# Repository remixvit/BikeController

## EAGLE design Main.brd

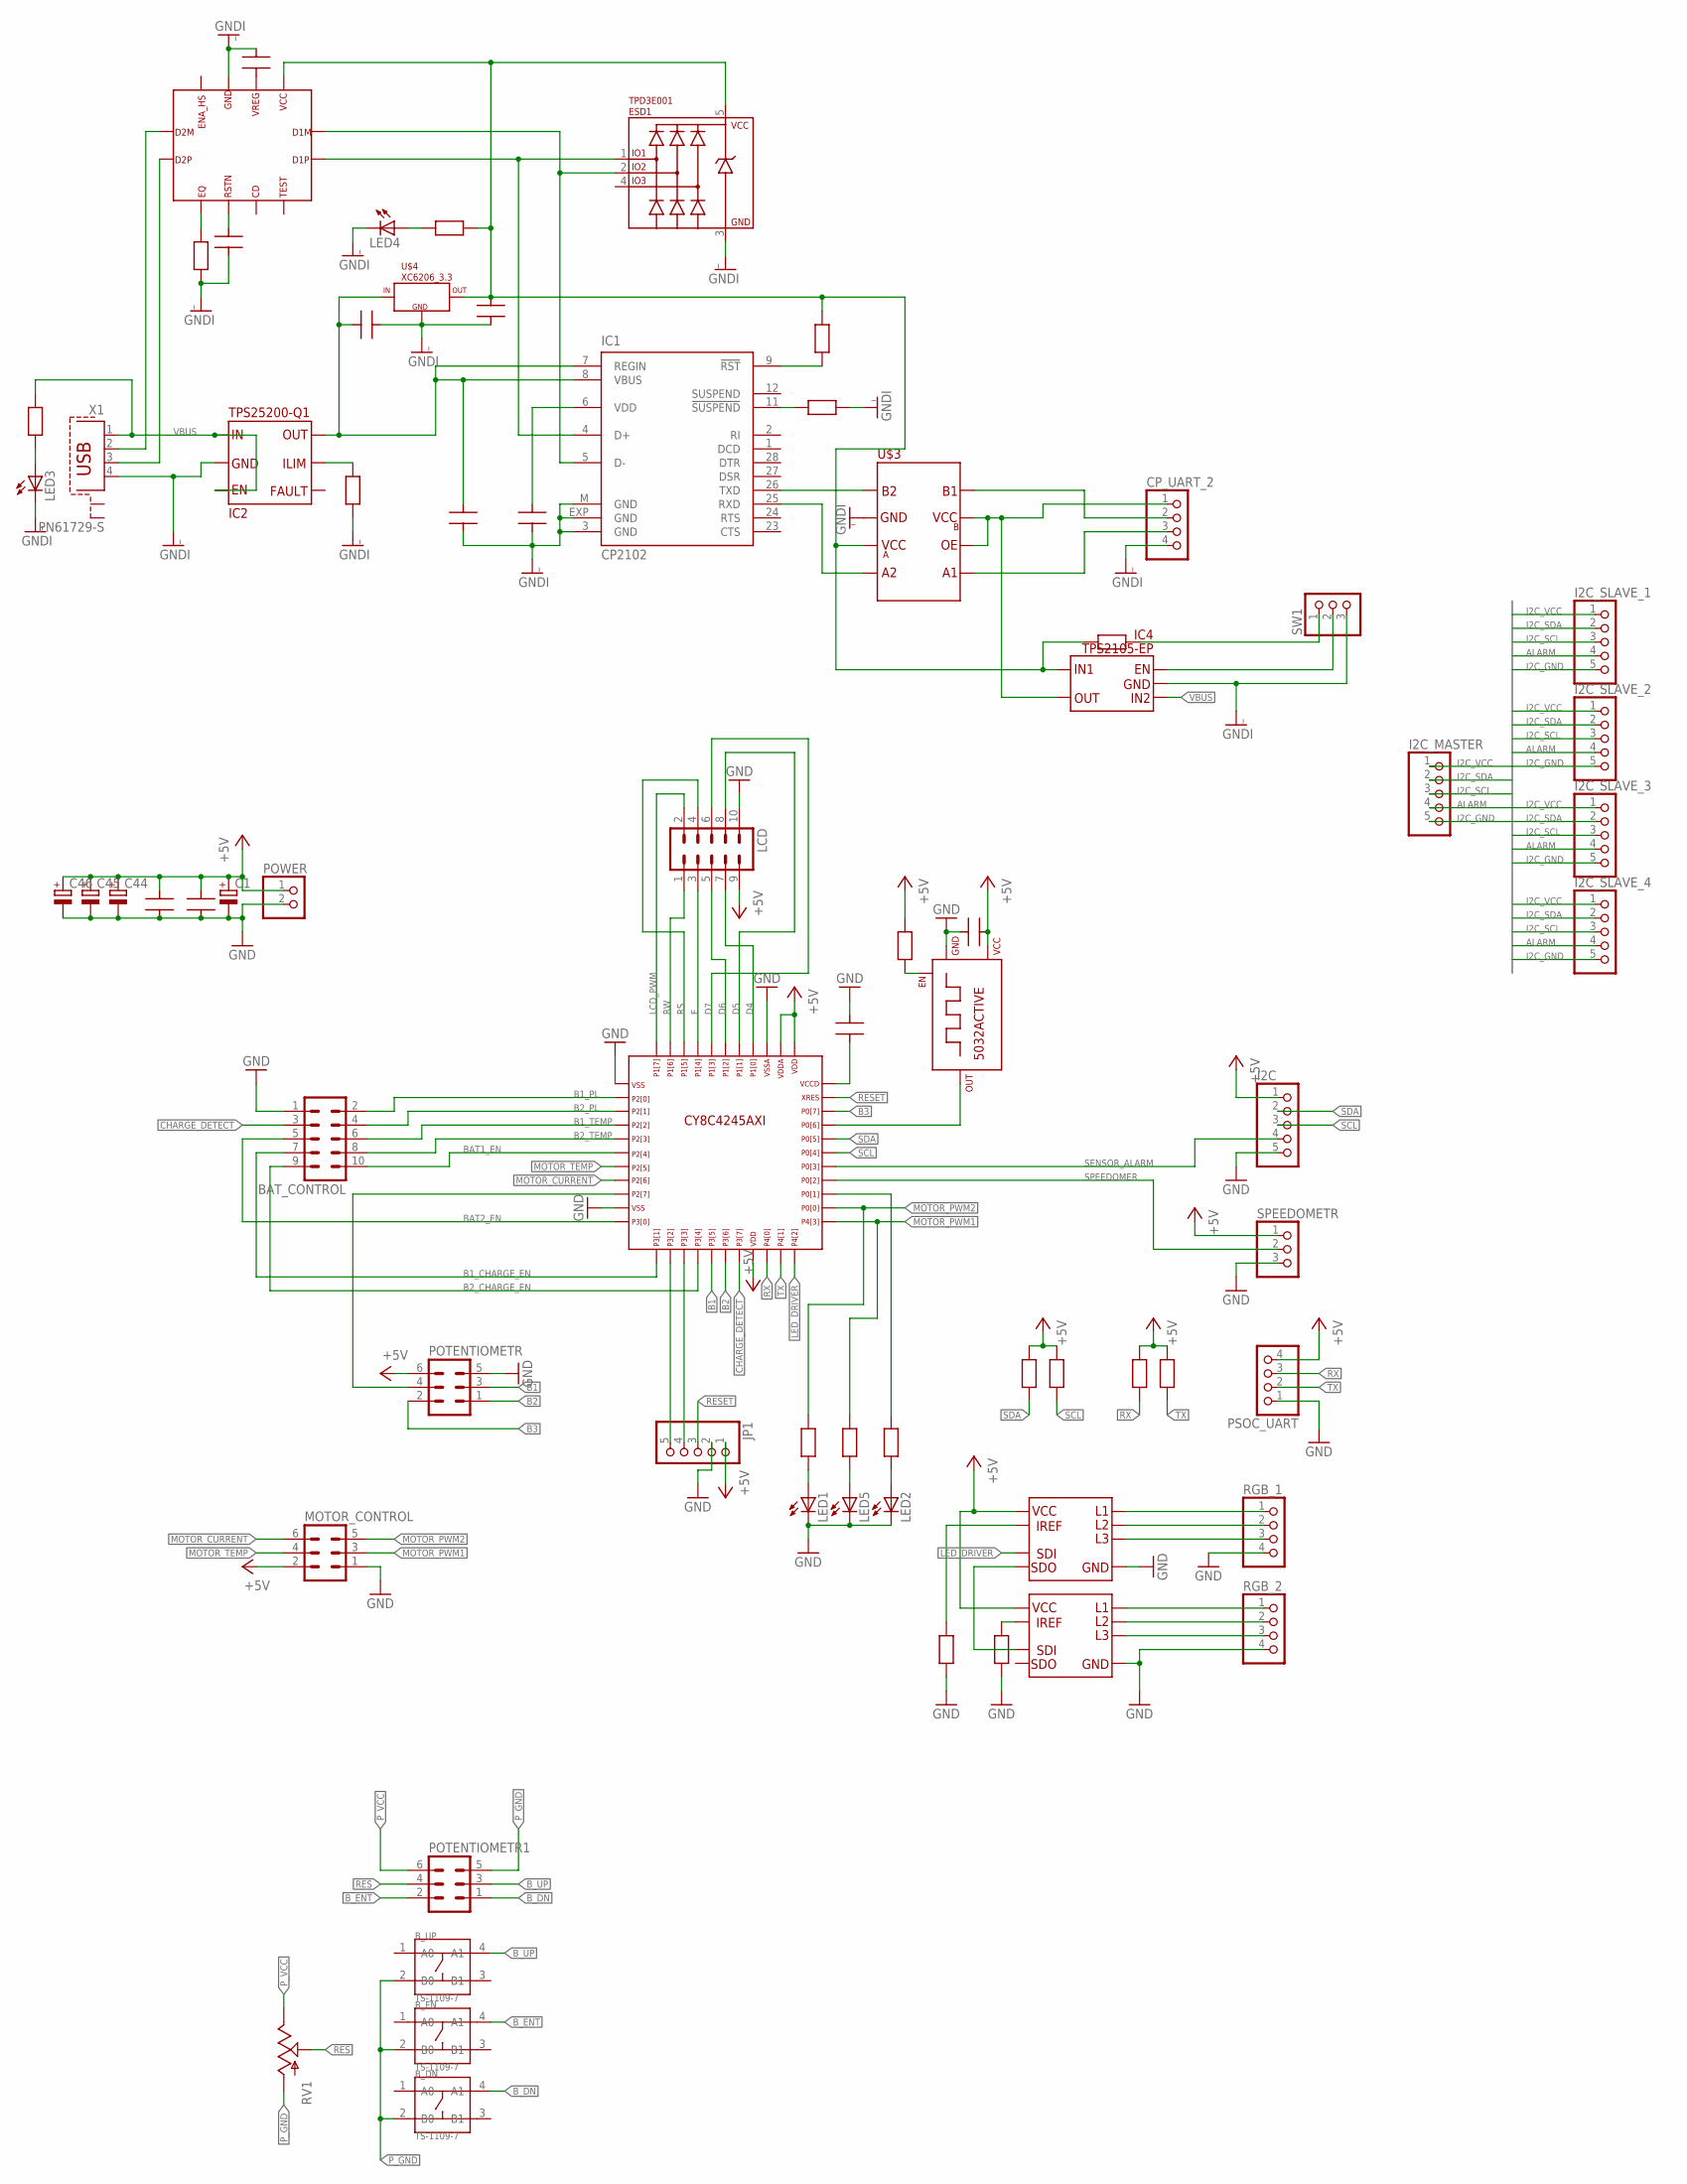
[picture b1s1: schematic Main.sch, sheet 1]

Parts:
BAT_CONTROL: ML10
B_DN: TS-1109-7; SW4-6.2X6.2X5.0MM
B_EN: TS-1109-7; SW4-6.2X6.2X5.0MM
B_UP: TS-1109-7; SW4-6.2X6.2X5.0MM
C1, C44: CPOL-EU150CLZ-0810; 150CLZ-0810
C2, C3, C4, C5, C6, C7, C8, C9, C10, C11: CAP0603; C0603
C45, C46: CPOL-EUSMCD; SMC_D
CP_UART_2: PINHD-1X4; 1X04
ESD1: TPD3E001; SOT23-5
I2C, I2C_MASTER, I2C_SLAVE_1, I2C_SLAVE_2, I2C_SLAVE_3, I2C_SLAVE_4: PINHD-1X5; 1X05
IC1: CP2102; MLP28
IC2: TPS25200-Q1; PWSON6
IC4: TPS2105-EP; SOT23-5
JP1: PINHD-1X5; 1X05
LCD: ML10
LED1, LED2, LED5: LEDCHIP-LED0603; CHIP-LED0603
LED3, LED4: LEDCHIP-LED0805; CHIP-LED0805
LED_DR1, LED_DR2: TLC5973; SOIC8-1.27-5X4MM
MOTOR_CONTROL: ML6
POTENTIOMETR, POTENTIOMETR1: ML6
POWER: PINHD-1X2; 1X02
PSOC_UART: PINHD-1X4; 1X04
R1, R2, R3, R4, R5, R6, R7, R8, R9, R10, R11, R12, R13, R14, R15, R16, R41: RES0603; R0603
RGB_1, RGB_2: PINHD-1X4; 1X04
RV1: POT; ALPS_POT
SPEEDOMETR: PINHD-1X3; 1X03
SW1: PINHD-1X3; 1X03
U$1: CY8C4245; TQFP44_CY_LOGO
U$2: 5032ACTIVE; 5030A
U$3: TXS0102_SM8; SM8
U$4: XC6206_3.3; SOT23
USB1: TUSB211QRWBRQ1; X2QFN
X1: PN61729-S

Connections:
+5V: C1.+, C2.2, C3.2, C5.2, C44.+, C45.+, C46.+, I2C.1, JP1.1, LCD.9, LED_DR1.8, LED_DR2.8, MOTOR_CONTROL.2, POTENTIOMETR.6, POWER.1, PSOC_UART.4, R1.2, R2.2, R3.2, R4.2, R7.2, SPEEDOMETR.1, U$1.19, U$1.34, U$1.35, U$2.4 (+5V)
ALARM: I2C_MASTER.4, I2C_SLAVE_1.4, I2C_SLAVE_2.4, I2C_SLAVE_3.4, I2C_SLAVE_4.4
B1: POTENTIOMETR.3, U$1.16
B1_CHARGE_EN: BAT_CONTROL.7, U$1.12
B1_PL: BAT_CONTROL.2, U$1.2
B1_TEMP: BAT_CONTROL.6, U$1.4
B2: POTENTIOMETR.1, U$1.17
B2_CHARGE_EN: BAT_CONTROL.9, U$1.15
B2_PL: BAT_CONTROL.4, U$1.3
B2_TEMP: BAT_CONTROL.8, U$1.5
B3: POTENTIOMETR.2, U$1.31
BAT1_EN: BAT_CONTROL.10, U$1.6
BAT2_EN: BAT_CONTROL.5, U$1.11
B_DN: B_DN.4 (A1), POTENTIOMETR1.1
B_ENT: B_EN.4 (A1), POTENTIOMETR1.2
B_UP: B_UP.4 (A1), POTENTIOMETR1.3
CHARGE_DETECT: BAT_CONTROL.3, U$1.18
D4: LCD.7, U$1.37
D5: LCD.8, U$1.38
D6: LCD.5, U$1.39
D7: LCD.6, U$1.40
E: LCD.3, U$1.41
GND: BAT_CONTROL.1, C1.-, C2.1, C3.1, C4.1, C5.1, C44.-, C45.-, C46.-, I2C.5, JP1.2, LCD.10, LED1.C, LED2.C, LED5.C, LED_DR1.4, LED_DR2.4, MOTOR_CONTROL.1, POTENTIOMETR.5, POWER.2, PSOC_UART.1, R10.1, R11.1, RGB_1.4, RGB_2.4, SPEEDOMETR.3, U$1.1, U$1.10, U$1.36, U$2.2 (GND)
GNDI: C6.1, C7.1, C8.1, C9.2, C10.1, C11.2, CP_UART_2.4, ESD1.3, IC1.3 (GND), IC1.EXP (GND), IC1.M (GND), IC2.EPAD, IC2.P$2, IC4.2, LED3.C, LED4.C, R9.1, R12.1, R15.1, SW1.3, U$3.GND, U$4.1 (GND), USB1.10, X1.4
I2C_GND: I2C_MASTER.5, I2C_SLAVE_1.5, I2C_SLAVE_2.5, I2C_SLAVE_3.5, I2C_SLAVE_4.5
I2C_SCL: I2C_MASTER.3, I2C_SLAVE_1.3, I2C_SLAVE_2.3, I2C_SLAVE_3.3, I2C_SLAVE_4.3
I2C_SDA: I2C_MASTER.2, I2C_SLAVE_1.2, I2C_SLAVE_2.2, I2C_SLAVE_3.2, I2C_SLAVE_4.2
I2C_VCC: I2C_MASTER.1, I2C_SLAVE_1.1, I2C_SLAVE_2.1, I2C_SLAVE_3.1, I2C_SLAVE_4.1
LCD_PWM: LCD.2, U$1.44
LED_DRIVER: LED_DR1.6, U$1.22
MOTOR_CURRENT: MOTOR_CONTROL.6, U$1.8
MOTOR_PWM1: MOTOR_CONTROL.3, R41.2, U$1.23
MOTOR_PWM2: MOTOR_CONTROL.5, R5.2, U$1.24
MOTOR_TEMP: MOTOR_CONTROL.4, U$1.7
unnamed: U$1.30, U$2.3 (OUT)
unnamed: C4.2, U$1.33
unnamed: JP1.5, U$1.13
unnamed: JP1.4, U$1.14
unnamed: IC2.P$1, IC2.P$3, R13.2, X1.1
unnamed: R6.2, U$1.25
unnamed: POTENTIOMETR.4, U$1.9
unnamed: R7.1, U$2.1 (EN)
unnamed: C9.1, ESD1.5, IC4.5, R8.2, R14.2, R16.1, U$3.VCCA, U$4.2 (OUT), USB1.12
unnamed: LED1.A, R5.1
unnamed: LED2.A, R6.1
unnamed: USB1.8, X1.2
unnamed: IC1.9 (!RST), R8.1
unnamed: CP_UART_2.2, U$3.B1
unnamed: IC1.11 (!SUSPEND), R9.2
unnamed: LED_DR1.5, LED_DR2.6
unnamed: ESD1.1, IC1.4 (D+), USB1.2
unnamed: LED_DR1.7, R11.2
unnamed: LED_DR2.7, R10.2
unnamed: LED_DR1.1, RGB_1.1
unnamed: LED_DR1.2, RGB_1.2
unnamed: LED_DR1.3, RGB_1.3
unnamed: LED_DR2.1, RGB_2.1
unnamed: LED_DR2.2, RGB_2.2
unnamed: LED_DR2.3, RGB_2.3
unnamed: ESD1.2, IC1.5 (D-), USB1.1
unnamed: IC2.P$5, R12.2
unnamed: CP_UART_2.3, U$3.A1
unnamed: R14.1, SW1.1
unnamed: USB1.7, X1.3
unnamed: LED3.A, R13.1
unnamed: LED4.A, R16.2
unnamed: C7.2, IC1.6 (VDD)
unnamed: IC1.26 (TXD), U$3.B2
unnamed: IC1.25 (RXD), U$3.A2
unnamed: IC4.1, SW1.2
unnamed: CP_UART_2.1, IC4.4, U$3.OE, U$3.VCCB
unnamed: C10.2, USB1.5
unnamed: R15.2, USB1.6
unnamed: C11.1, USB1.11
unnamed: LED5.A, R41.1
P_GND: B_DN.2 (B0), B_EN.2 (B0), B_UP.2 (B0), POTENTIOMETR1.5, RV1.P$3 (A)
P_VCC: POTENTIOMETR1.6, RV1.P$1 (E)
RES: POTENTIOMETR1.4, RV1.P$2 (S)
RESET: JP1.3, U$1.32
RS: LCD.4, U$1.42
RW: LCD.1, U$1.43
RX: PSOC_UART.3, R3.1, U$1.20
SCL: I2C.3, R2.1, U$1.28
SDA: I2C.2, R1.1, U$1.29
SENSOR_ALARM: I2C.4, U$1.27
SPEEDOMER: SPEEDOMETR.2, U$1.26
TX: PSOC_UART.2, R4.1, U$1.21
VBUS: C6.2, C8.2, IC1.7 (REGIN), IC1.8 (VBUS), IC2.P$6, IC4.3, U$4.3 (IN)

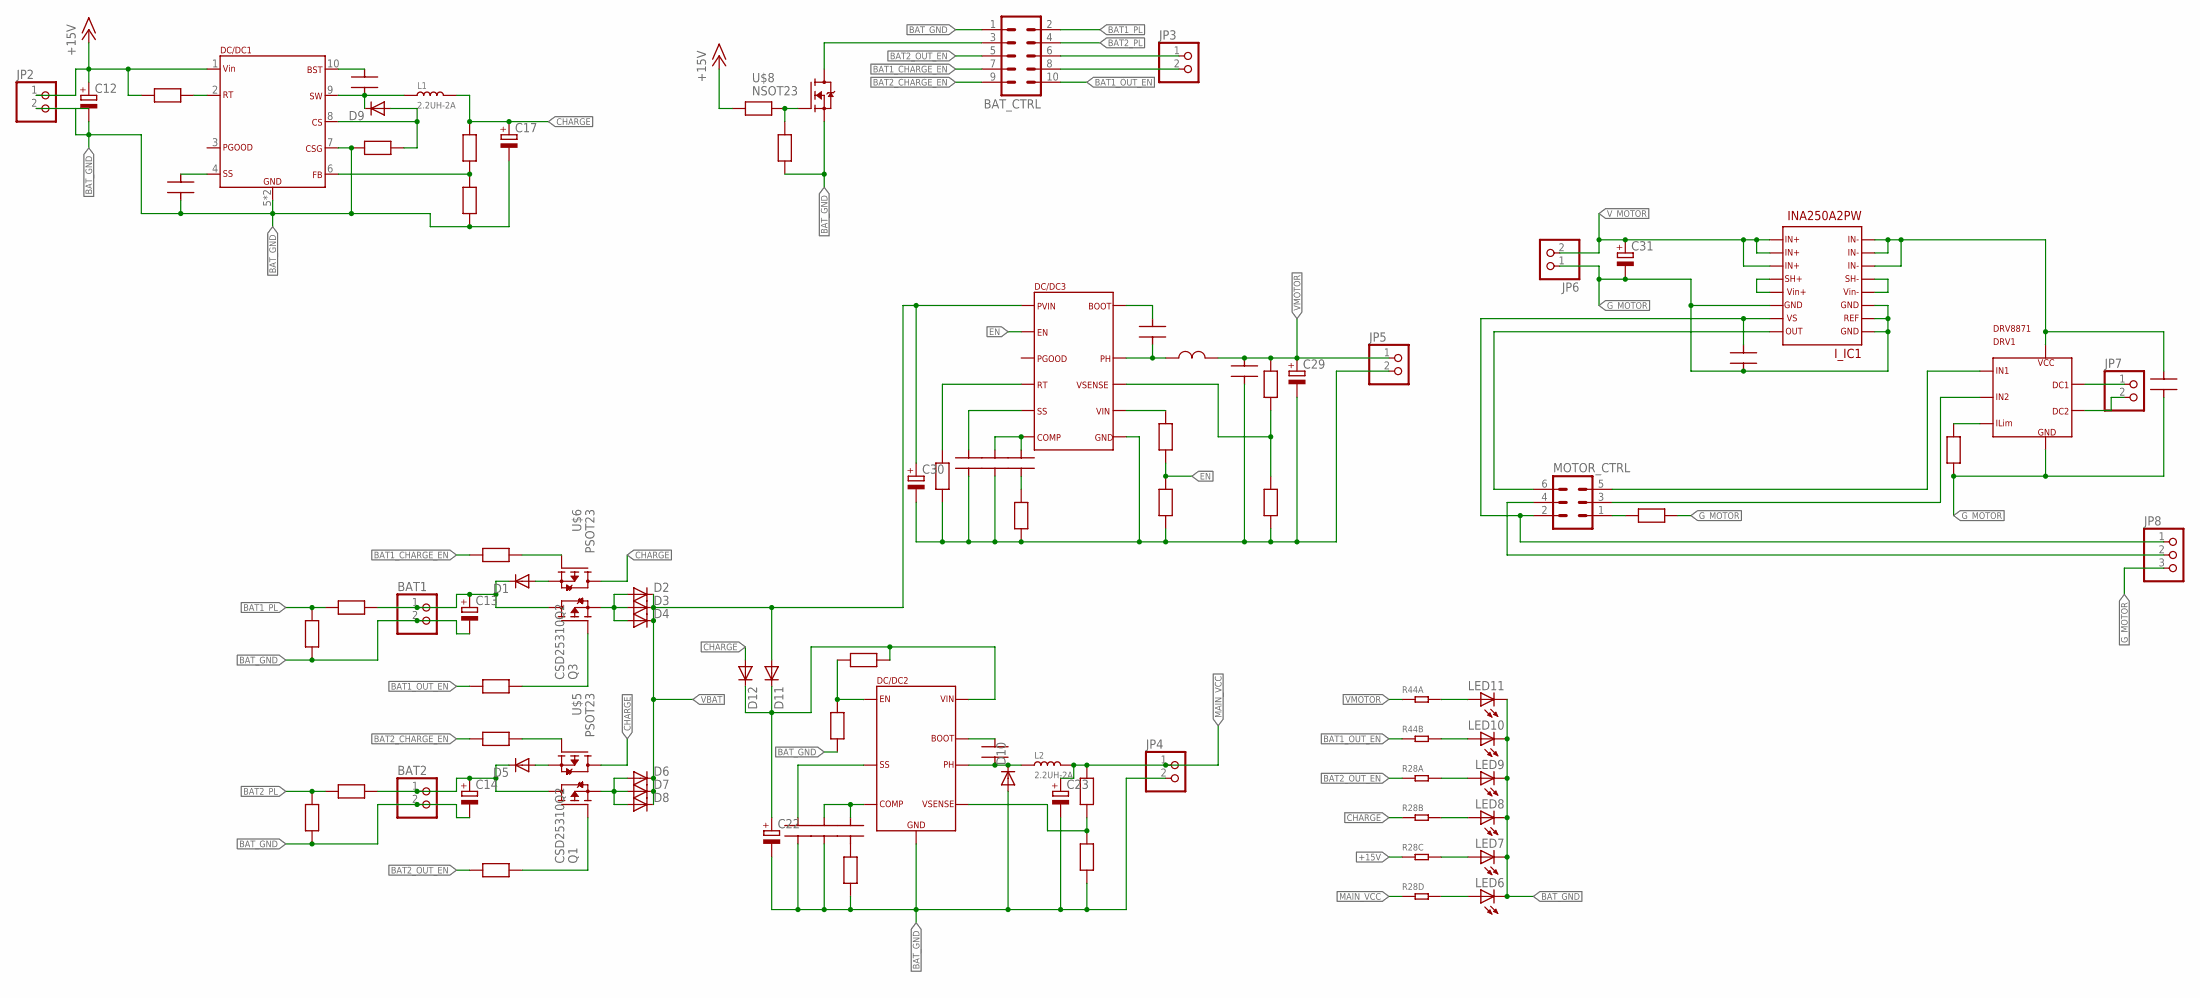
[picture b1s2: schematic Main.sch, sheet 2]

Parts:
BAT1, BAT2: PINHD-1X2; 1X02
BAT_CTRL: ML10
C12, C13, C14: CPOL-EU153CLV-0810; 153CLV-0810
C15, C16, C18, C19, C20, C21, C24, C25, C26, C27, C28, C32, C33: CAP0603; C0603
C17, C22, C23, C29, C30, C31: CPOL-EU153CLV-0505; 153CLV-0505
D1, D2, D3, D4, D5, D6, D7, D8, D10, D11, D12: DIODE-DO-214AC; DO-214AC
D9: DIODE-MELF-MLL41; MELF-MLL41
DC/DC1: LM25011; HVSSOP-10
DC/DC2: TPS54232; SOIC8-1.27-5X4MM
DC/DC3: TPS54622; VQFN-14_PWR
DRV1: DRV8871; HTSOP8
I_IC1: INA250A2PW; SSOP16
JP2, JP3, JP4, JP5, JP6, JP7: PINHD-1X2; 1X02
JP8: PINHD-1X3; 1X03
L1, L2: 2.2UH-2A; INT2-SMD-4.8X4.6X1.0MM
L$1: LDCP
LED6, LED7, LED8, LED9, LED10, LED11: LEDCHIPLED_1206; CHIPLED_1206
MOTOR_CTRL: ML6
Q1, Q3: CSD25310Q2; SON_Q2
R17, R18, R19, R20, R21, R22, R23, R24, R25, R26, R27, R29, R30, R31, R32, R33, R34, R35, R36, R37, R38, R39, R40, R42, R43, R45, R46: RES0603; R0603
R28, R44: RES-ARRAY-1206; RA1206-8
U$5, U$6: PSOT23; SOT23
U$8: NSOT23; SOT23W

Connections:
+15V: C12.+, DC/DC1.1, JP2.1, R25.2, R28.3 (1), R42.1
BAT1_CHARGE_EN: BAT_CTRL.7, R24.1
BAT1_OUT_EN: BAT_CTRL.10, R23.1, R44.2 (1)
BAT1_PL: BAT_CTRL.2, R17.2, R18.2
BAT2_CHARGE_EN: BAT_CTRL.9, R22.1
BAT2_OUT_EN: BAT_CTRL.5, R21.1, R28.1
BAT2_PL: BAT_CTRL.4, R19.1, R20.1
BAT_GND: BAT1.2, BAT2.2, BAT_CTRL.1, C12.-, C13.-, C14.-, C15.1, C17.-, C18.1, C20.1, C22.-, C23.-, C24.1, C25.1, C28.1, C29.-, C30.-, D10.A, DC/DC1.5, DC/DC1.7, DC/DC1.EPAD (5), DC/DC2.7, DC/DC3.2 (7), DC/DC3.3 (7), DC/DC3.EPAD_BIG (7), DC/DC3.EPAD_M1 (7), DC/DC3.EPAD_M2 (7), DC/DC3.EPAD_M3 (7), DC/DC3.EPAD_M4 (7), JP2.2, JP4.2, JP5.2, LED6.C, LED7.C, LED8.C, LED9.C, LED10.C, LED11.C, R17.1, R19.2, R26.2, R29.1, R30.1, R32.1, R33.1, R35.1, R36.1, R38.1, R40.1, R43.1, U$8.S
CHARGE: C17.+, D12.A, L1.2, R27.1, R28.2 (1), U$5.S, U$6.S
EN: DC/DC3.10 (2), R37.2, R38.2
G_MOTOR: C31.-, C32.2, C33.2, DRV1.1, DRV1.7 (1), DRV1.EPAD_B (1), DRV1.EPAD_T (1), DRV1.EPAD_VIA1 (1), DRV1.EPAD_VIA2 (1), DRV1.EPAD_VIA3 (1), DRV1.EPAD_VIA4 (1), DRV1.EPAD_VIA5 (1), DRV1.EPAD_VIA6 (1), I_IC1.P$6, I_IC1.P$7, I_IC1.P$8, I_IC1.P$11, JP6.1, JP8.3, R45.1, R46.1
MAIN_VCC: C23.+, JP4.1, L2.2, R28.4 (1), R34.2
unnamed: BAT_CTRL.6, JP3.1
unnamed: BAT_CTRL.8, JP3.2
unnamed: BAT_CTRL.3, U$8.D
unnamed: D2.A, D3.A, D4.A, Q3.4 (D), Q3.D
unnamed: D1.A, U$6.D
unnamed: BAT1.1, C13.+, D1.C, Q3.1 (S), Q3.2 (S), Q3.5 (S), Q3.6 (S), Q3.S, R18.1
unnamed: Q3.3 (G), R23.2
unnamed: BAT2.1, C14.+, D5.C, Q1.1 (S), Q1.2 (S), Q1.5 (S), Q1.6 (S), Q1.S, R20.2
unnamed: R24.2, U$6.G
unnamed: R42.2, R43.2, U$8.G
unnamed: D6.A, D7.A, D8.A, Q1.4 (D), Q1.D
unnamed: D5.A, U$5.D
unnamed: Q1.3 (G), R21.2
unnamed: R22.2, U$5.G
unnamed: LED11.A, R44.8 (2)
unnamed: DC/DC1.2, R25.1
unnamed: C15.2, DC/DC1.4
unnamed: DC/DC1.6, R26.1, R27.2
unnamed: LED10.A, R44.7 (2)
unnamed: D9.A, DC/DC1.8, R29.2
unnamed: C16.1, D9.C, DC/DC1.9, L1.1
unnamed: C16.2, DC/DC1.10
unnamed: DC/DC2.3, R30.2, R31.2
unnamed: LED9.A, R28.8 (2)
unnamed: C19.1, R32.2
unnamed: C18.2, C19.2, DC/DC2.6
unnamed: C24.2, DC/DC3.9 (5)
unnamed: C20.2, DC/DC2.4
unnamed: DC/DC3.1 (4), R35.2
unnamed: C21.2, DC/DC2.1
unnamed: C21.1, D10.C, DC/DC2.8, L2.1
unnamed: DC/DC2.5, R33.2, R34.1
unnamed: LED8.A, R28.7 (2)
unnamed: C25.2, C26.2, DC/DC3.8 (6)
unnamed: C26.1, R36.2
unnamed: DC/DC3.6 (8), R37.1
unnamed: C27.2, DC/DC3.13 (11)
unnamed: C27.1, DC/DC3.11 (10), DC/DC3.12 (10), L$1.P$1
unnamed: DC/DC3.7 (9), R39.2, R40.2
unnamed: LED7.A, R28.6 (2)
unnamed: LED6.A, R28.5 (2)
unnamed: I_IC1.P$12, I_IC1.P$13
unnamed: I_IC1.P$4, I_IC1.P$5
unnamed: MOTOR_CTRL.1, R46.2
unnamed: C33.1, DRV1.5, I_IC1.P$1, I_IC1.P$2, I_IC1.P$3
unnamed: DRV1.3, MOTOR_CTRL.5
unnamed: DRV1.2, MOTOR_CTRL.3
unnamed: DRV1.4, R45.2
unnamed: DRV1.6, JP7.1
unnamed: DRV1.8, JP7.2
unnamed: C32.1, I_IC1.P$10, JP8.1, MOTOR_CTRL.2
unnamed: I_IC1.P$9, MOTOR_CTRL.6
unnamed: JP8.2, MOTOR_CTRL.4
unnamed: C22.+, D11.C, D12.C, DC/DC2.2, R31.1
VBAT: C30.+, D2.C, D3.C, D4.C, D6.C, D7.C, D8.C, D11.A, DC/DC3.4 (1), DC/DC3.5 (1)
VMOTOR: C28.2, C29.+, JP5.1, L$1.P$2, R39.1, R44.1
V_MOTOR: C31.+, I_IC1.P$14, I_IC1.P$15, I_IC1.P$16, JP6.2

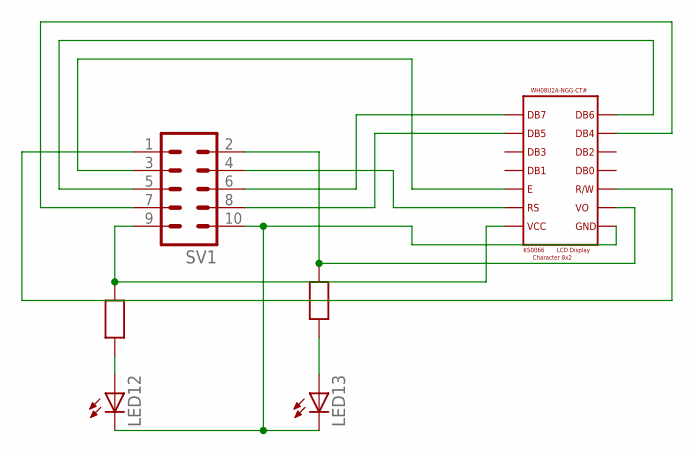
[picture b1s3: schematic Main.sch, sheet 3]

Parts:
LED12, LED13: LEDCHIPLED_1206; CHIPLED_1206
R47, R48: RES0603; R0603
SV1: ML10
U$7: 8X2_KS066; 7X2

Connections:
unnamed: R47.2, SV1.9, U$7.2
unnamed: LED12.C, LED13.C, SV1.10, U$7.1
unnamed: SV1.7, U$7.11
unnamed: SV1.5, U$7.13
unnamed: SV1.3, U$7.6
unnamed: SV1.1, U$7.5
unnamed: SV1.8, U$7.12
unnamed: SV1.6, U$7.14
unnamed: SV1.4, U$7.4
unnamed: R48.2, SV1.2, U$7.3
unnamed: LED12.A, R47.1
unnamed: LED13.A, R48.1

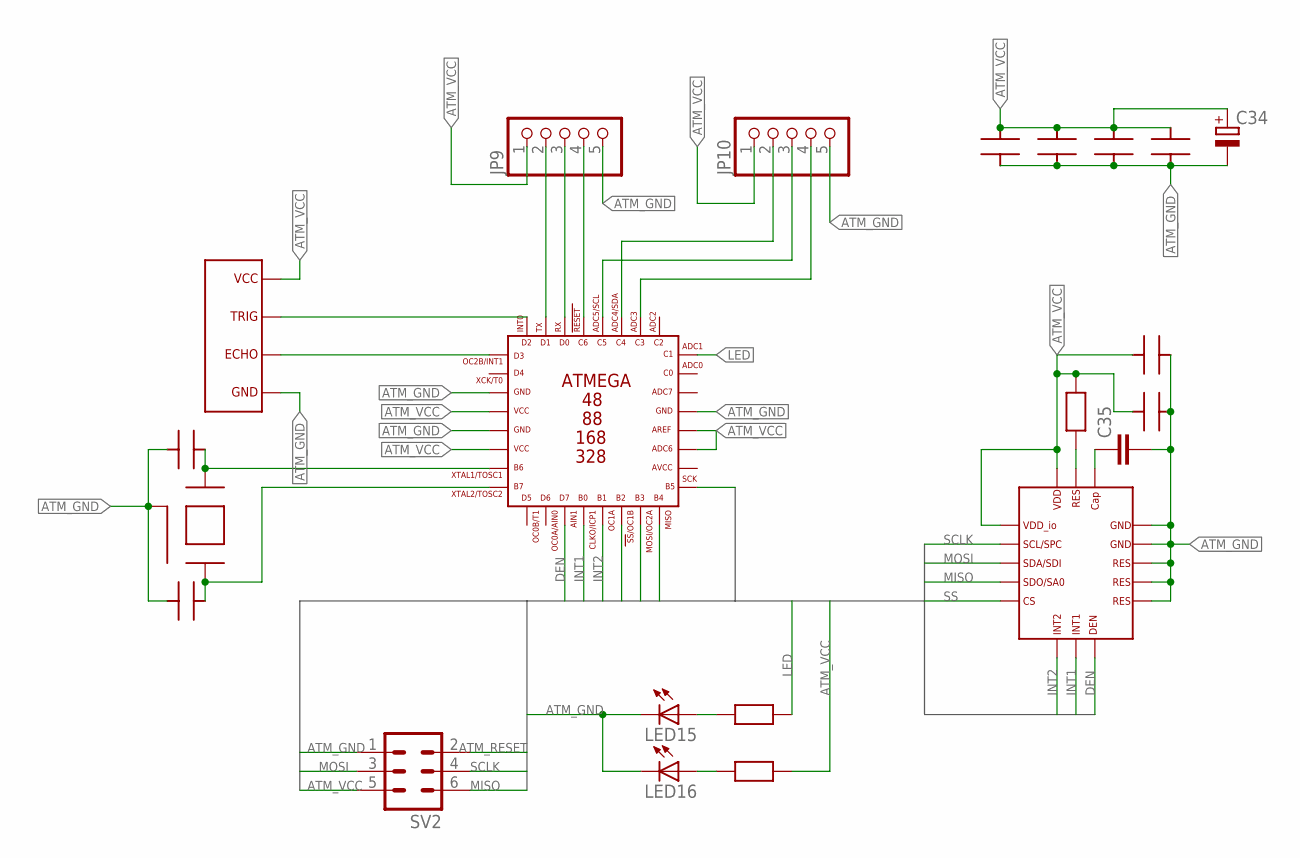
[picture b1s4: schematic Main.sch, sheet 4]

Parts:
C34: CPOL-EU153CLV-0505; 153CLV-0505
C35: C-EUC1206; C1206
C36, C37, C38, C39, C40, C41, C42, C43: CAP0603; C0603
GYRO1: L3GD20H; LGA_3X3_16
JP9, JP10: PINHD-1X5; 1X05
LED15, LED16: LEDCHIPLED_0603; CHIPLED_0603
LIDAR1: HC-SR04
R49, R50, R51: RES0603; R0603
SV2: ML6
U$9: ATMEGAN8; TQFP32-08
U$10: 3225PASSIVE; 3225

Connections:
ATM_GND: C34.-, C35.2, C36.2, C37.2, C38.1, C39.1, C40.1, C41.1, C42.1, C43.1, GYRO1.9, GYRO1.10, GYRO1.11, GYRO1.12, GYRO1.13, JP9.5, JP10.5, LED15.C, LED16.C, LIDAR1.4, SV2.1, U$9.GND, U$9.GND1, U$9.GND2, U$10.2, U$10.4
ATM_RESET: JP9.4, SV2.2, U$9.C6
ATM_VCC: C34.+, C36.1, C37.1, C38.2, C39.2, C40.2, C41.2, GYRO1.1, GYRO1.16, JP9.1, JP10.1, LIDAR1.1, R49.2, R51.1, SV2.5, U$9.ADC6, U$9.AREF, U$9.VCC, U$9.VCC1
DEN: GYRO1.8, U$9.D7
INT1: GYRO1.7, U$9.B0
INT2: GYRO1.6, U$9.B1
LED: R50.1, U$9.C1
MISO: GYRO1.4, SV2.6, U$9.B4
MOSI: GYRO1.3, SV2.3, U$9.B3
unnamed: JP9.2, U$9.D1
unnamed: JP9.3, U$9.D0
unnamed: LED15.A, R50.2
unnamed: JP10.2, U$9.C4
unnamed: JP10.3, U$9.C5
unnamed: JP10.4, U$9.C3
unnamed: LIDAR1.3, U$9.D3
unnamed: LIDAR1.2, U$9.D2
unnamed: C43.2, U$9.B6, U$10.1
unnamed: C42.2, U$9.B7, U$10.3
unnamed: LED16.A, R51.2
unnamed: GYRO1.15, R49.1
unnamed: C35.1, GYRO1.14
SCLK: GYRO1.2, SV2.4, U$9.B5
SS: GYRO1.5, U$9.B2

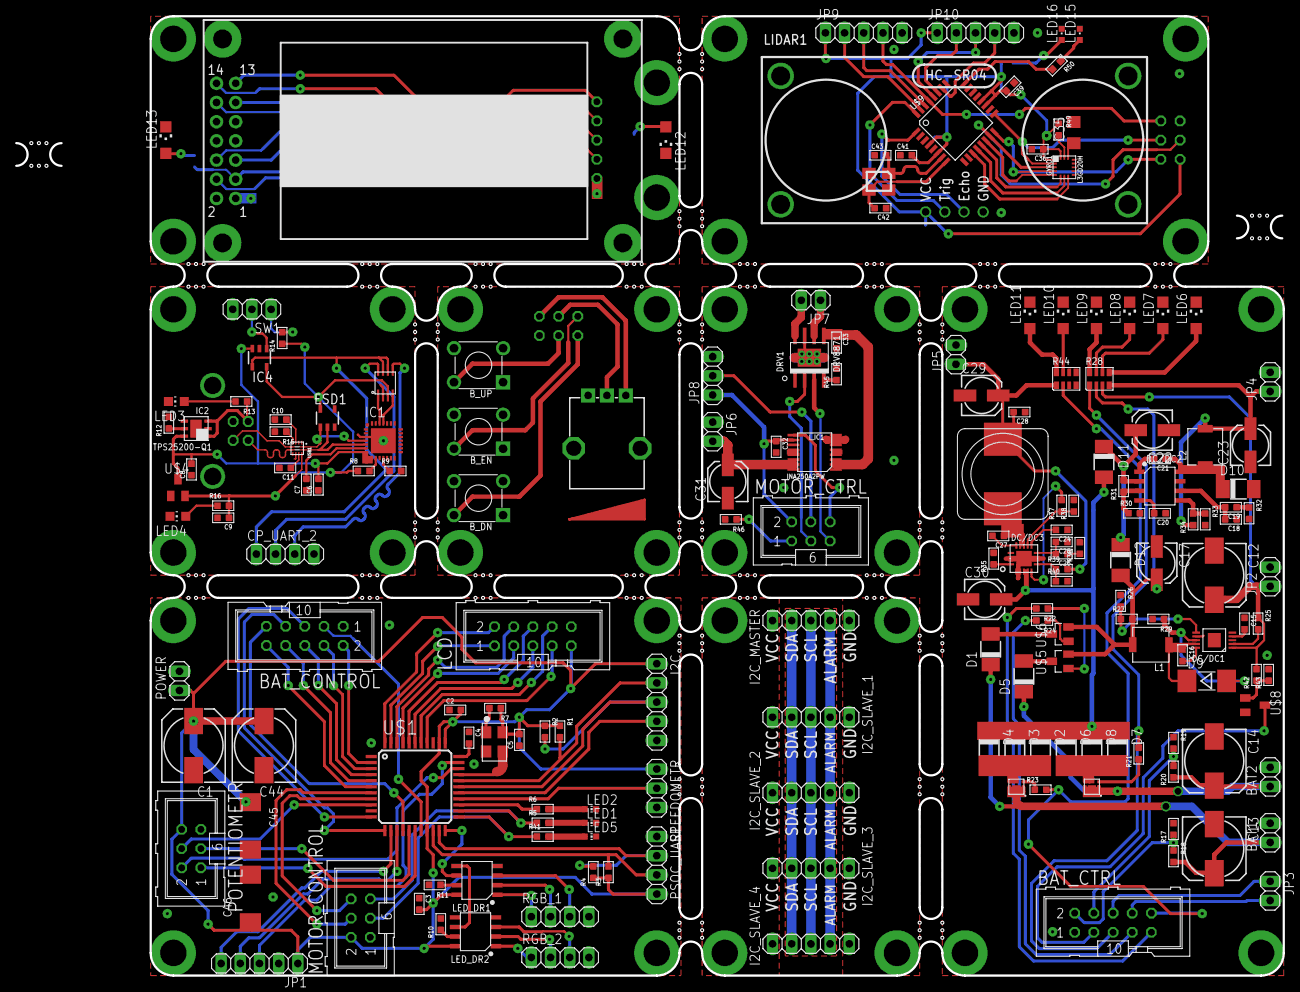
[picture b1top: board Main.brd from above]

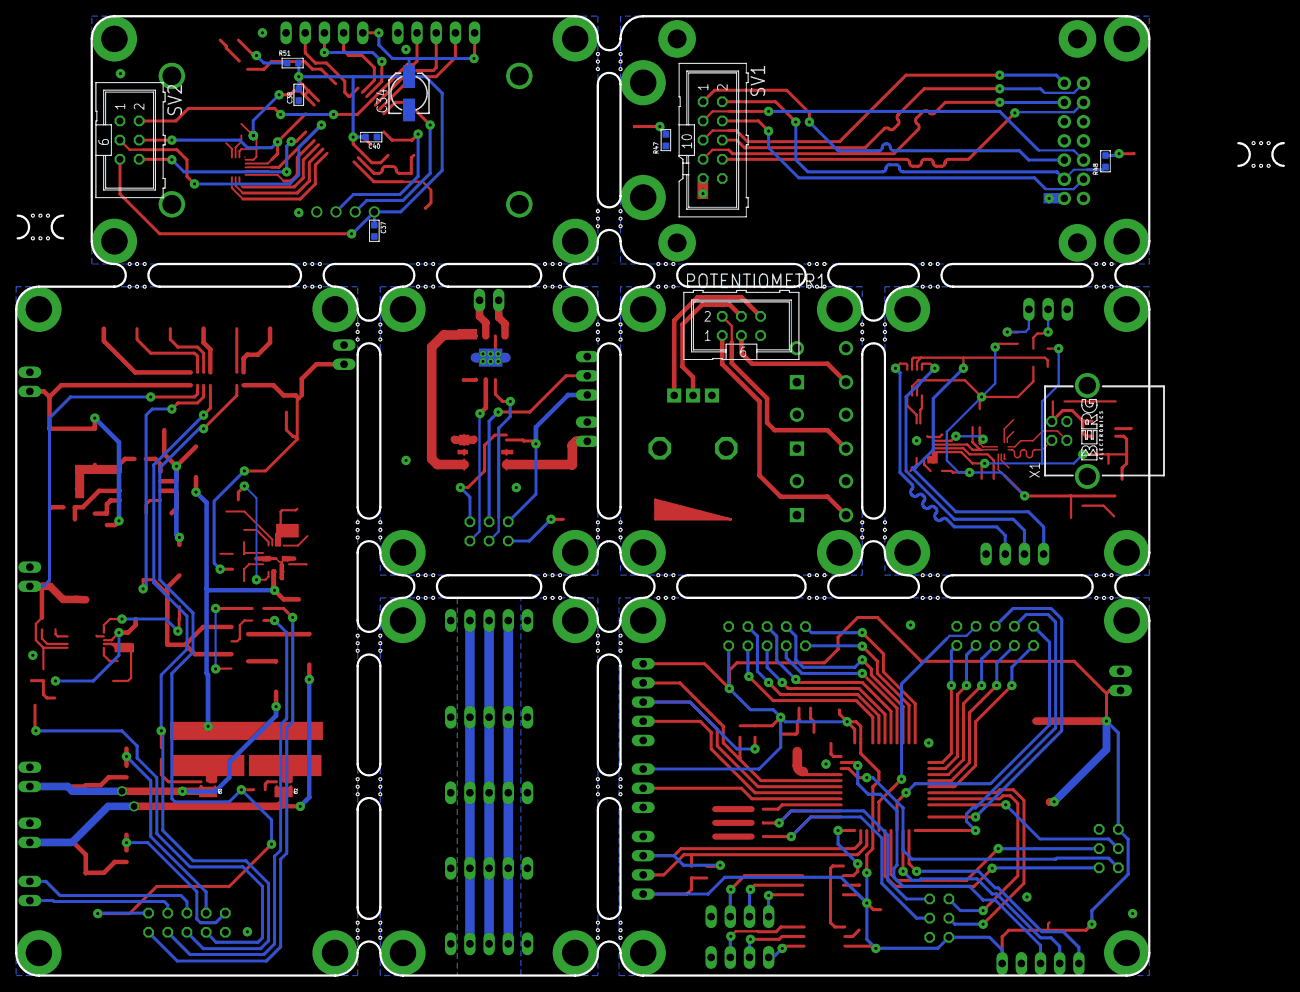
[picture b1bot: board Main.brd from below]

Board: 2 copper layers, 150.0 x 127.0 mm, 192 parts (11 on the bottom side), 193 nets.

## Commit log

2016-01-14 Create shematic and route pcb for Bike Controller Project

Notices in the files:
parts and their libraries:
SparkFun-Electromechanical: Licensing: Creative Commons ShareAlike 4.0 International - https://creativecommons.org/licenses/by-sa/4.0
